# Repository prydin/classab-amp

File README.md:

# 50W Class AB Amplifier

## Disclaimer
This amplifier has been built and testad and, at least subjectively speaking, sounds great. However, I'm not a professional designer
and this is my first "serious" attempt at amplifier design. I invite you to build this amplifier if you like, but don't expect it to
perform like a professionally designed high-end amplifier. That said, I think it sounds pretty darn good. 

## Background
This is my take on a classic Class AB amplifier. I did it for two reasons: I wanted to learn how to design and build a Class AB amplifier and
I needed better sound than crappy Bluetooth speakers in my office. I settled for 50W because that's all the power I need for my application
and the voltages involved are a lot more forgiving than what you'd have with a 300W monster. 

Some people have said it looks a lot like Doug Self's "Blameless Amplifier". I take that as a compliment, but the fact is that I didn't even
know how Self was when I started building it. The design is just based on various ideas from other amplifiers that I put together and tried to
make it my own.

## Repository structure
* `kicad` - Schematic and PCB layout in KiCAD format
*  `spice` - LTSpice simulations

## Overall design
The design is a simple single differential stage amplifier with a single transistor VAS driving two Darlington pairs for the final current 
gain stage. 

### Input stage
After the customary DC-blocking capacitor and RF filter, the signal is fed into a long tailed pair differential amplifier that's enhanced to 
an active current sink and current mirror loads. The active sink and load helps improve both distortion and frequency response. The bias 
current of the LTP is set to approximately 600uA. The LTP and its current mirrors are mounted on a separate copper island for maximum heat
condudctivity between the transistors. The feedback is fed through a 22k/1k voltage divider, yielding about 23x amplification. This is a 
conservative estimate and may have to be adjusted when testing the physical build. The active current sink and load seem to offer a robust
power supply rejection. 

### Voltage amplification/drive stage
I went for a very simple single-sided design here. I've gotten many suggestions that I should try a dual differential design instead, but 
the current design seems good enough, so I stuck with it. The VAS has a 47p compensation capacitor which appears to be enough to provide 
ample phase margin. After some testing, I also found that a 4.7nF Miller capacitance on the VAS current sink greatly helped to maintain 
stability.

### Output stage biasing
The output stage is biased using a servo transistor driven by a constant current sink. The BD139 for the servo as chosen just because it's
easy to mount on a heat sink together with the power components for good heat conductivity between components. A much less powerful 
transistor works too, but would have been harder to attach to the heat sink.

### Output stage
Here I am using some very common components. BD139/BD140 transistors as the first stage of the Darlington pair and MJL3281/MLJ1302 for
the final stage. The final transistors can handle 200W, so they are definitely a bit overkill. However, they performed better than
TIP35/TIP36 in the simulator and headroom is never a bad thing to have. Before the signal reaches the speaker, it is passed through
a snubber and a Zobel network to further improve stability.

### Short circuit projection 
To protect against short circuits, overcurrent and catastrophic DC output, two transistors are fitted that measure the curremt across
the degeneration resistors and shut off the base current to the final Darlington stage when the current reaches approximately 4A. 

### Output coil
The output coil is realized simply by winding 10-12 turns of 16 AWG wire around R21. See the photo below!

### Power improvements
Altough this hasn't been tested or thorouhgly analyzed, it should be possible to increase the rail voltages to +-40V, which yields about
160W according to simultions. For this to work, the gain needs to be made higher by increasing the value of the feedback resistor. The
voltage divider for the short circuit protection also needs to be adjusted to allow more curent. Finally, the biasing may need to be adjusted
as well. 

### Stability
The amplifier is very stable in simulations, but my original design suffered from some 800-900kHz 200mV p/p oscillations at idle. After 
some troubleshooting, it turned out that the bias circuitry had some local stability issues. To remedy this, a 4.7nF Miller capacitance was
added to Q8. I also found that a larger capacitance (~50nF) across collector and emitter on Q8 helped with stability. The CE capacitance was
later omitted due to bandwidth concerns. 

### Power supply
The amplifier is intended to be powered by an unregulated linear power supply like the one supplied in this repository. Each amplifier board
is fitted with 4700uF on each rail, per channel and the rectifier board has an additional 4700uF on each rail. In simulations, measurements 
and listening tests, this seems sufficient. However, the rectifier board has room for two additional capacitors if so desired.

In my build, I'm using a 2x25V toroidial transformer. Where I live, this ended up giving me 2x39V rectified voltage, which is a bit more
than I would have liked, especially since it puts the BC547/557 very close to their CE voltage limit. So I would recommend you either go 
with a slightly lower voltage or swap the transistors in the differential stage to 2N5551/5401 or something simiar. 

### PCB Design
I am *NOT* an expert at PCB design. In fact, I'm very much a novice and not very good at it, so the PCB layout is probably somewhat naive. 
I settled for a ground plane and laterally adjacent power planes rather than star ground. That said, with proper ground wiring, there is 
no audible hiss or hum. If you have ideas on how to improve the PCB design (or the overall design), feel free to fork and issue a pull
request. I'll take any help I can get.

# Build and bring-up

## Mechanincal design
Mechnical design is not my forte, so you're probably best off to come up with your own design here. I went with a 12' x 12' metal case
and found that it easily fit all the components. In my 50W design, I'm simply using the case as heat sink. This works well for any power
you would put out in a normal home and the case get barely luke warm. For higher power levels or listening at a sustained high volume, 
a dedicated, finned heat sink is probably a better option.

## Thermal coupling
It is *extremely* important that Q7, Q8, Q9, Q10 and Q12 are thermally coupled, i.e. mounted on the same heat sink. Failure to do this 
may result in thermal runaway and catastrophic damage to the output stage! 

## Bring-up
This is the procedure I followed when bringing it up the first time. It saved me on the first bring-up since I had accidentally mixed up 
the transistors in the LTP which put DC on the speaker output.

1. Disconnect the speakers.
2. Turn the bias trimmer to its lowest setting (highest resistance)
3. Connect a current limited power supply with -12V, 0V and +12V to the power inputs. Limit the current to 200mA. The amplifier should draw less than 100mA.
4. Measure the DC voltage across the speaker terminals. It should be less than 50mV. 
5. Connect an oscilloscope to the output. There should be no oscillations.
6. Slowly bring the voltage to +/-24V. The current draw should still be well below 100mA.
7. Connect a 8Ω resistive dummy load to the output. The current draw should not increase significantly.
8. Connect a signal generator to the input and send in a 10mV p/p 1kHz sine singal. You should see approximately 200mV p/p on the speaker output.
9. Increase the current limit to 500mA and try the same with a 100mV p/p and 200mV p/p signal.
10. Increase the current limit to 1A and try a 300mV p/p input.
11. Connect the speakers and feed a music signal. It it may not sound perfect, since lab supplies aren't designed to power amplifiers, but there should be no severe distortion. 
13. Hook up the amplifier to the power supply that will be used for the final build. I put 3A fuses in series with each rail.
14. Measure DC voltage on the speaker outputs. The DC voltage 
15. Measure the voltage between the emitters on the output transistors (Q10 and Q12). Adjust the bias trim until the voltage reaches 8mV. This corresponds to a bias current of 18mA. You may go higher or lower depending on your preferences. Just watch the temperatures!
16. Bring up the amplifer and test it using a dummy load and signal generator as described above.
17. If all has gone well up until this point, connect your speakers and crank up your favorite tune. ENJOY!

# Schematic

## SPICE simulations

All simulations are done with an 8 ohm resistive dummy load, 1V input at 1kHz.

### THD
At a fairly moderate quiescent current of 15mA, I get a THD of 0.019%. A THD below 0.1% is considered to be inaudible, so these numbers
are fine by me. I know there are audiophiles who insist on THD numbers <0.0001%, but I'm not one of them. Inaudible is just fine by me.

I've gotten suggestions that adding an emitter follower to the VAS might improve THD. I might try that, but I have a feeling there will 
be more pressing matters than getting the THD even more inaudible. 

```Fourier components of V(out)
DC component:-0.00675533

Harmonic	Frequency	 Fourier 	Normalized	 Phase  	Normalized
 Number 	  [Hz]   	Component	 Component	[degree]	Phase [deg]
    1   	 1.000e+3	 2.087e+1	 1.000e+0	   90.66°	    0.00°
    2   	 2.000e+3	 1.490e-3	 7.140e-5	  -77.43°	 -168.10°
    3   	 3.000e+3	 3.155e-4	 1.512e-5	   38.31°	  -52.35°
    4   	 4.000e+3	 3.378e-4	 1.619e-5	  106.45°	   15.78°
    5   	 5.000e+3	 5.623e-4	 2.694e-5	 -129.10°	 -219.76°
    6   	 6.000e+3	 7.723e-5	 3.700e-6	  129.91°	   39.24°
    7   	 7.000e+3	 3.638e-4	 1.743e-5	 -163.17°	 -253.83°
    8   	 8.000e+3	 6.704e-5	 3.213e-6	 -144.07°	 -234.73°
    9   	 9.000e+3	 3.393e-4	 1.626e-5	 -174.70°	 -265.37°
   10   	 1.000e+4	 1.427e-4	 6.838e-6	 -141.03°	 -231.69°
Partial Harmonic Distortion: 0.008339%
Total Harmonic Distortion:   0.018652%
```

### AC Analysis
The amplifier has a 3dB bandwidth of about 121kHz, which is respectable, while not in the hardcore audiophile range, but it keeps any poles far away from the audible 
range to make both the amplitude and phase response vritually flat where it matters. I am of the opinion that nothing >20kHz has any impact on
the listening experience.

### Open Loop Gain and Phase Margin
The DC open loop gain is about 50dB, giving the global loop about a 27dB feedback level. I understand there are many different theories around this, but the concensus seems
to be that 20-40dB is an appropriate level. 

The phase margin is about 53 degrees according to simulations, which should be a respectable number and quite stable. It's probably good enough
that I could lower or completely eliminate the VAS Miller capacitance. But it doesn't affect bandwith much, so for now, I'll keep it around. If you build the amp
and end up experimenting with the compensation, please let me know what the results were!

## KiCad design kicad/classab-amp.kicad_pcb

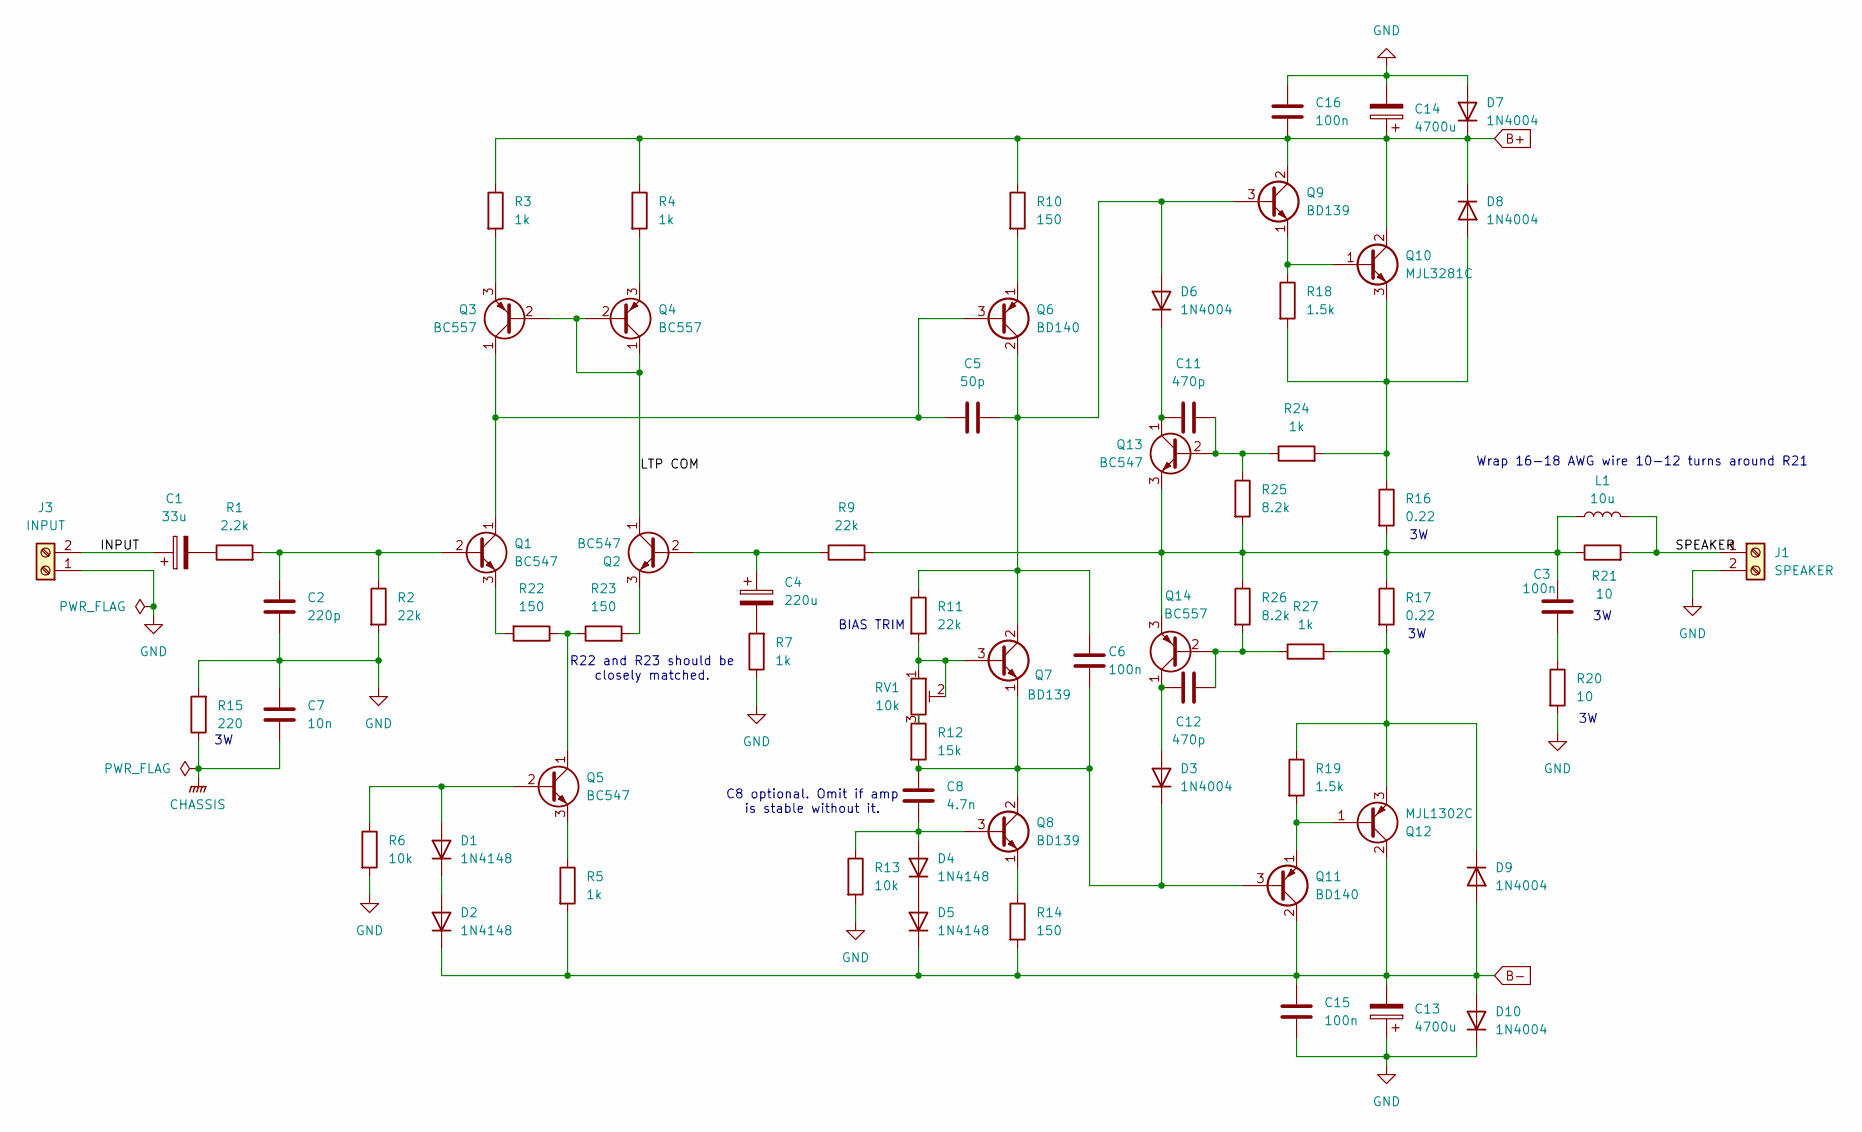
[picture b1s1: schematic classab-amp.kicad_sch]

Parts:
C1: 33u; CP_Radial_D4.0mm_P1.50mm
C2: 220p; C_Rect_L7.2mm_W3.0mm_P5.00mm_FKS2_FKP2_MKS2_MKP2
C3, C6, C15, C16: 100n; C_Rect_L7.2mm_W3.0mm_P5.00mm_FKS2_FKP2_MKS2_MKP2
C4: 220u; CP_Radial_D8.0mm_P5.00mm
C5: 50p; C_Rect_L7.2mm_W3.0mm_P5.00mm_FKS2_FKP2_MKS2_MKP2
C7: 10n; C_Rect_L7.2mm_W3.0mm_P5.00mm_FKS2_FKP2_MKS2_MKP2
C8: 4.7n; C_Rect_L7.2mm_W3.0mm_P5.00mm_FKS2_FKP2_MKS2_MKP2
C11, C12: 470p; C_Rect_L7.2mm_W3.0mm_P5.00mm_FKS2_FKP2_MKS2_MKP2
C13, C14: 4700u; CP_Radial_D18.0mm_P7.50mm
D1, D2, D4, D5: 1N4148; D_DO-35_SOD27_P7.62mm_Horizontal
D3, D6, D7, D8, D9, D10: 1N4004; D_DO-41_SOD81_P10.16mm_Horizontal
J1: SPEAKER; TerminalBlock_Phoenix_MKDS-1,5-2_1x02_P5.00mm_Horizontal
J3: INPUT; TerminalBlock_4Ucon_1x02_P3.50mm_Horizontal
L1: 10u; CP_Radial_D4.0mm_P1.50mm
Q1, Q2, Q5, Q13: BC547; TO-92_Inline
Q3, Q4, Q14: BC557; TO-92_Inline
Q6, Q11: BD140; TO-126-3_Vertical
Q7, Q8, Q9: BD139; TO-126-3_Vertical
Q10: MJL3281C; TO-264-3_Vertical
Q12: MJL1302C; TO-264-3_Vertical
R1: 2.2k; R_Axial_DIN0204_L3.6mm_D1.6mm_P7.62mm_Horizontal
R2, R9, R11: 22k; R_Axial_DIN0204_L3.6mm_D1.6mm_P7.62mm_Horizontal
R3, R4, R5, R7, R24, R27: 1k; R_Axial_DIN0204_L3.6mm_D1.6mm_P7.62mm_Horizontal
R6, R13: 10k; R_Axial_DIN0204_L3.6mm_D1.6mm_P7.62mm_Horizontal
R10, R14, R22, R23: 150; R_Axial_DIN0204_L3.6mm_D1.6mm_P7.62mm_Horizontal
R12: 15k; R_Axial_DIN0204_L3.6mm_D1.6mm_P7.62mm_Horizontal
R15: 220; R_Axial_DIN0414_L11.9mm_D4.5mm_P15.24mm_Horizontal
R16, R17: 0.22; R_Axial_DIN0414_L11.9mm_D4.5mm_P15.24mm_Horizontal
R18, R19: 1.5k; R_Axial_DIN0204_L3.6mm_D1.6mm_P7.62mm_Horizontal
R20, R21: 10; R_Axial_DIN0414_L11.9mm_D4.5mm_P15.24mm_Horizontal
R25, R26: 8.2k; R_Axial_DIN0204_L3.6mm_D1.6mm_P7.62mm_Horizontal
RV1: 10k; TRIM_T93YA103KT20

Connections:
/INPUT: C1.1, J3.2
/LTP COM: Q2.1 (C), Q3.2 (B), Q4.1 (C), Q4.2 (B)
/SPEAKER: J1.1, L1.2, R21.2
B+: C14.1, C16.2, D7.1 (K), D8.1 (K), Q9.2 (C), Q10.2 (C), R3.1, R4.1, R10.1
B-: C13.2, C15.1, D2.1 (K), D5.1 (K), D9.2 (A), D10.2 (A), Q11.2 (C), Q12.2 (C), R5.2, R14.2
CHASSIS: C7.2, R15.1
GND: C2.2, C7.1, C13.1, C14.2, C15.2, C16.1, D7.2 (A), D10.1 (K), J1.2, J3.1, R2.2, R6.2, R7.1, R13.2, R15.2, R20.2
unnamed: C1.2, R1.1
unnamed: C3.2, R20.1
unnamed: C4.2, R7.2
unnamed: D1.2 (A), Q5.2 (B), R6.1
unnamed: D1.1 (K), D2.2 (A)
unnamed: C12.1, D3.2 (A), Q14.1 (C)
unnamed: C6.2, C8.1, D3.1 (K), Q7.1 (E), Q8.2 (C), Q11.3 (B), R12.2
unnamed: C8.2, D4.2 (A), Q8.3 (B), R13.1
unnamed: D4.1 (K), D5.2 (A)
unnamed: C5.2, C6.1, D6.2 (A), Q6.2 (C), Q7.2 (C), Q9.3 (B), R11.1
unnamed: C11.1, D6.1 (K), Q13.1 (C)
unnamed: D8.2 (A), Q10.3 (E), R16.1, R18.2, R24.2
unnamed: D9.1 (K), Q12.3 (E), R17.2, R19.1, R27.2
unnamed: C2.1, Q1.2 (B), R1.2, R2.1
unnamed: C5.1, Q1.1 (C), Q3.1 (C), Q6.3 (B)
unnamed: Q1.3 (E), R22.2
unnamed: C4.1, Q2.2 (B), R9.1
unnamed: Q2.3 (E), R23.2
unnamed: Q3.3 (E), R3.2
unnamed: Q4.3 (E), R4.2
unnamed: Q5.1 (C), R22.1, R23.1
unnamed: Q5.3 (E), R5.1
unnamed: Q6.1 (E), R10.2
unnamed: Q7.3 (B), R11.2, RV1.1, RV1.2
unnamed: Q8.1 (E), R14.1
unnamed: Q9.1 (E), Q10.1 (B), R18.1
unnamed: Q11.1 (E), Q12.1 (B), R19.2
unnamed: C11.2, Q13.2 (B), R24.1, R25.1
unnamed: C3.1, L1.1, Q13.3 (E), Q14.3 (E), R9.2, R16.2, R17.1, R21.1, R25.2, R26.1
unnamed: C12.2, Q14.2 (B), R26.2, R27.1
unnamed: R12.1, RV1.3

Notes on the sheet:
Wrap 16-18 AWG wire 10-12 turns around R21
R22 and R23 should be closely matched.
BIAS TRIM
C8 optional. Omit if amp is stable without it.

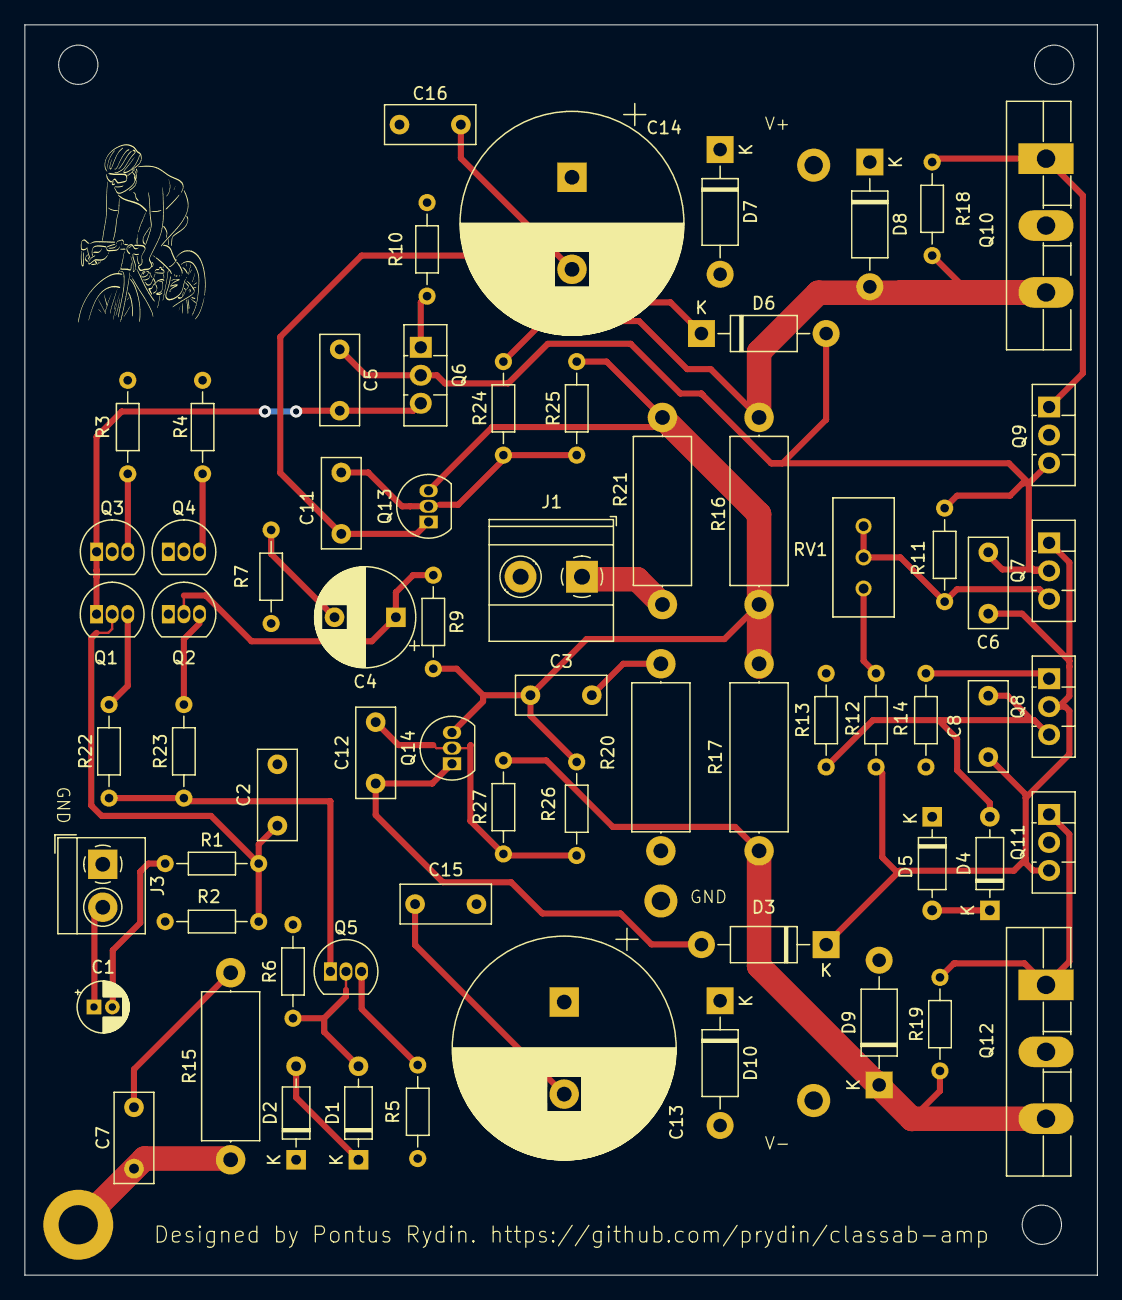
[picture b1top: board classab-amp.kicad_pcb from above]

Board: 2 copper layers, 87.4 x 101.9 mm, 68 parts (0 on the bottom side), 38 nets.

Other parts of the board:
PIC1: LOGO

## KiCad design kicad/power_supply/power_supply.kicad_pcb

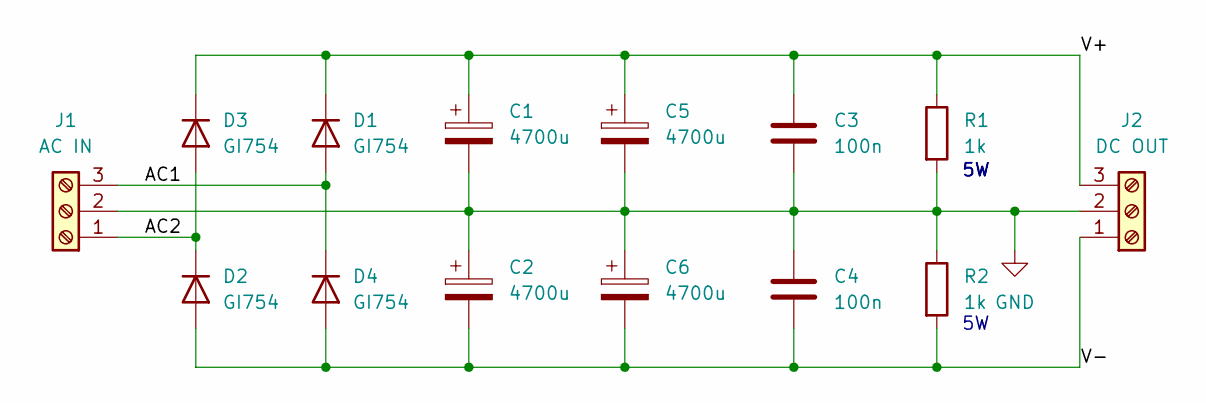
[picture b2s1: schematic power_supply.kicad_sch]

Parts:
C1, C2, C5, C6: 4700u; CP_Radial_D18.0mm_P7.50mm
C3, C4: 100n; C_Rect_L7.2mm_W5.5mm_P5.00mm_FKS2_FKP2_MKS2_MKP2
D1, D2, D3, D4: GI754; D_P600_R-6_P12.70mm_Horizontal
J1: AC IN; TerminalBlock_Phoenix_PT-1,5-3-3.5-H_1x03_P3.50mm_Horizontal
J2: DC OUT; TerminalBlock_Phoenix_PT-1,5-3-3.5-H_1x03_P3.50mm_Horizontal
R1, R2: 1k; R_Axial_DIN0414_L11.9mm_D4.5mm_P15.24mm_Horizontal

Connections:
/AC1: D1.2 (A), D4.1 (K), J1.3
/AC2: D2.1 (K), D3.2 (A), J1.1
/V+: C1.1, C3.1, C5.1, D1.1 (K), D3.1 (K), J2.3, R1.1
/V-: C2.2, C4.2, C6.2, D2.2 (A), D4.2 (A), J2.1, R2.2
GND: C1.2, C2.1, C3.2, C4.1, C5.2, C6.1, J1.2, J2.2, R1.2, R2.1

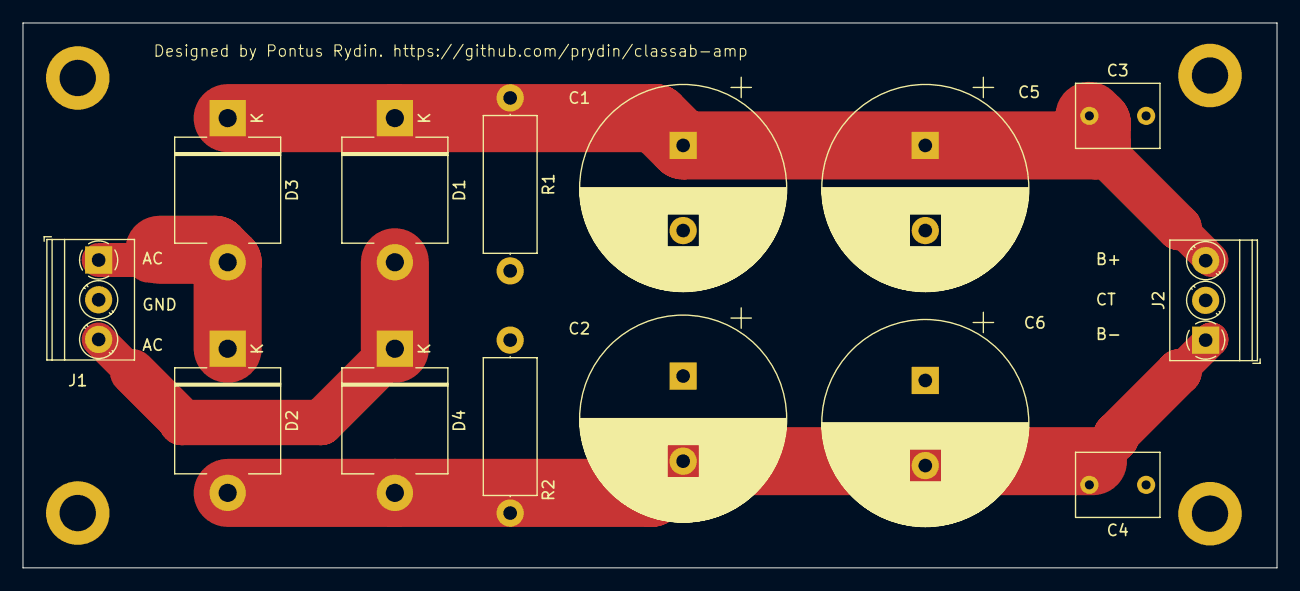
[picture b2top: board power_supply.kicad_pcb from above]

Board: 2 copper layers, 110.5 x 48.0 mm, 14 parts (0 on the bottom side), 5 nets.

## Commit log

2024-08-27 Added gitignore
2024-08-27 Fixed typos, tried to get SPICE working
2024-08-27 Moved power supply to separate project
2024-08-29 Improvements based on suggestions from various people
2024-08-30 PCB layout
2024-08-31 v1.0
2024-09-01 Power supply
2024-09-01 Finished power supply
2024-09-01 Added images
2024-09-02 Updated THD numbers
2024-09-10 Post 1.0 adjutments
2024-09-18 Post build adjustments
2024-09-19 Adjustments
2024-09-19 Updated FFT screenshot
2024-09-19 Added Zobel image
2024-09-19 Added coil image
2024-09-19 Added coil
2024-09-20 Added ver 2 SPICE design
2024-09-25 1.1 RC
2024-09-26 Updated schematic
2024-09-26 Update gerber files
2024-09-27 Added chassis pic
2024-09-28 Updated Bode plot
2024-09-28 Added LTP degeneration
2024-09-29 Changed chassis pic
2024-09-29 Added new phase margin plot
